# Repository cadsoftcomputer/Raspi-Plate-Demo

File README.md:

# Raspi-Plate-Demo

This is an H-Bridge and IR LED Pi Hat for controlling the Rasperry Pi with an IR Remote Control.

The following sites were instrumental in setting up LIRC and having Python interface with it.
* https://piface.github.io/pifacecad/lirc.html
* http://alexba.in/blog/2013/01/06/setting-up-lirc-on-the-raspberrypi/
* http://ozzmaker.com/2013/10/24/how-to-control-the-gpio-on-a-raspberry-pi-with-an-ir-remote/

This site helped with setting up the Python script to run on boot.
* http://www.raspberrypi-spy.co.uk/2013/07/running-a-python-script-at-boot-using-cron/

The PiHat standard as defined by the Raspberry Pi Foundation
* https://github.com/raspberrypi/hats

All of the Python code was made to run under Python3 however it's likely that it will run under Python2 since the python-lirc library works in both versions of Python.

The EAGLE design files were made using V7 of EAGLE. The PiHat_Standard_Outline.lbr contains packages that conform to the PiHat standard.

For any questions or concerns contact support@cadsoftusa.com or call 954-237-0932.

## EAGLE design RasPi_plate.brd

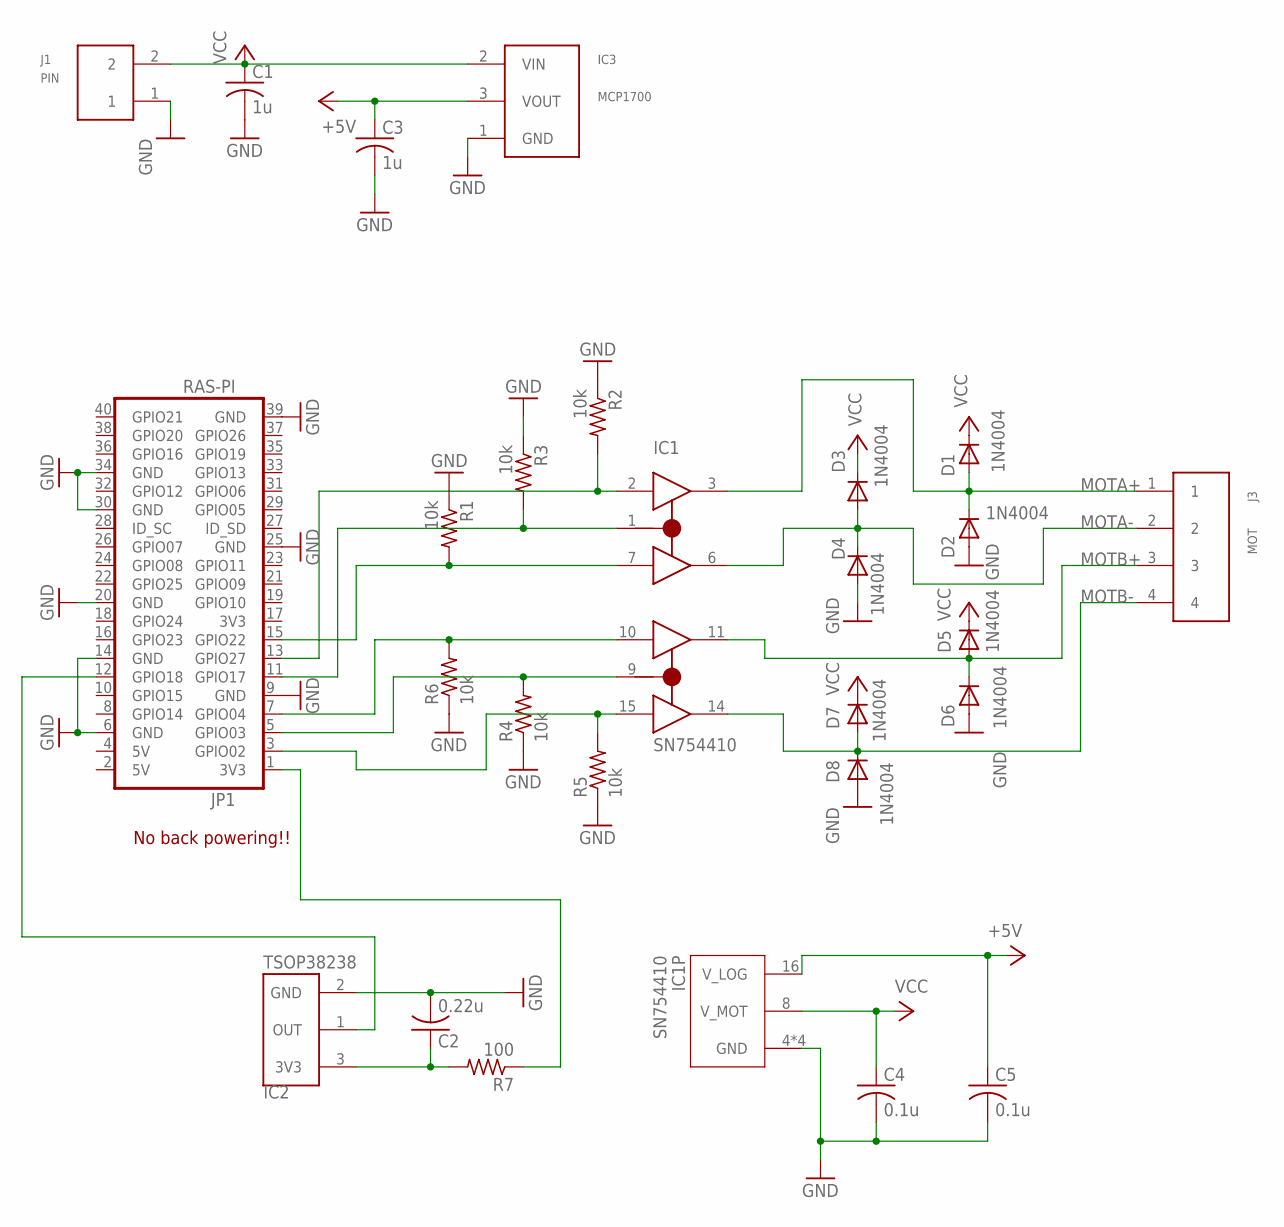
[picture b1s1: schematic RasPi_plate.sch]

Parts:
C1, C3: 1u; C0805; MPN EMK212B7105KD-T
C2: 0.22u; C0805; MPN MC0805B224M250CT
C4, C5: 0.1u; C0805; MPN C2012X7R1H104K085AA
D1, D2, D3, D4, D5, D6, D7, D8: 1N4004; DO41-10; MPN 1N4007-E3/54
IC1: SN754410; DIL16; MPN SN754410NE
IC2: TSOP38238; MPN TSOP38238
IC3: MCP1700; TO92; MPN MCP1700-5002E/TO
J1: PIN; 2PINHEAD
J3: MOT; 4PINHEAD
JP1: RAS-PI; 2X20
R1, R2, R3, R4, R5, R6: 10k; R0805; MPN MCHP05W4F1002T5E
R7: 100; R0805; MPN MCHP05W4F1000T5E

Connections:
1EN: IC1.1 (1,2EN), JP1.11 (GPIO17), R3.2
+3V3: C3.1, C5.1, IC1.16 (V_LOG), IC3.3 (VOUT)
GND: C1.2, C2.2, C3.2, C4.2, C5.2, D2.A, D4.A, D6.A, D8.A, IC1.4 (GND), IC1.5 (GND), IC1.12 (GND), IC1.13 (GND), IC2.2 (GND), IC3.1 (GND), J1.1, JP1.6 (GND), JP1.9 (GND), JP1.14 (GND), JP1.20 (GND), JP1.25 (GND), JP1.30 (GND), JP1.34 (GND), JP1.39 (GND), R1.1, R2.1, R3.1, R4.1, R5.1, R6.1
MOTA+: D1.A, D2.C, IC1.3 (1Y), J3.1
MOTA-: D3.A, D4.C, IC1.6 (2Y), J3.2
MOTB+: D5.A, D6.C, IC1.11 (3Y), J3.3
MOTB-: D7.A, D8.C, IC1.14 (4Y), J3.4
unnamed: IC1.7 (2A), JP1.15 (GPIO22), R1.2
unnamed: IC1.10 (3A), JP1.7 (GPIO04), R6.2
unnamed: IC1.9 (3,4EN), JP1.5 (GPIO03), R4.2
unnamed: IC2.1 (OUT), JP1.12 (GPIO18)
unnamed: C2.1, IC2.3 (3V3), R7.2
unnamed: JP1.1 (3V3), R7.1
unnamed: IC1.2 (1A), JP1.13 (GPIO27), R2.2
unnamed: IC1.15 (4A), JP1.3 (GPIO02), R5.2
VCC: C1.1, C4.1, D1.C, D3.C, D5.C, D7.C, IC1.8 (V_MOT), IC3.2 (VIN), J1.2

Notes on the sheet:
No back powering!!

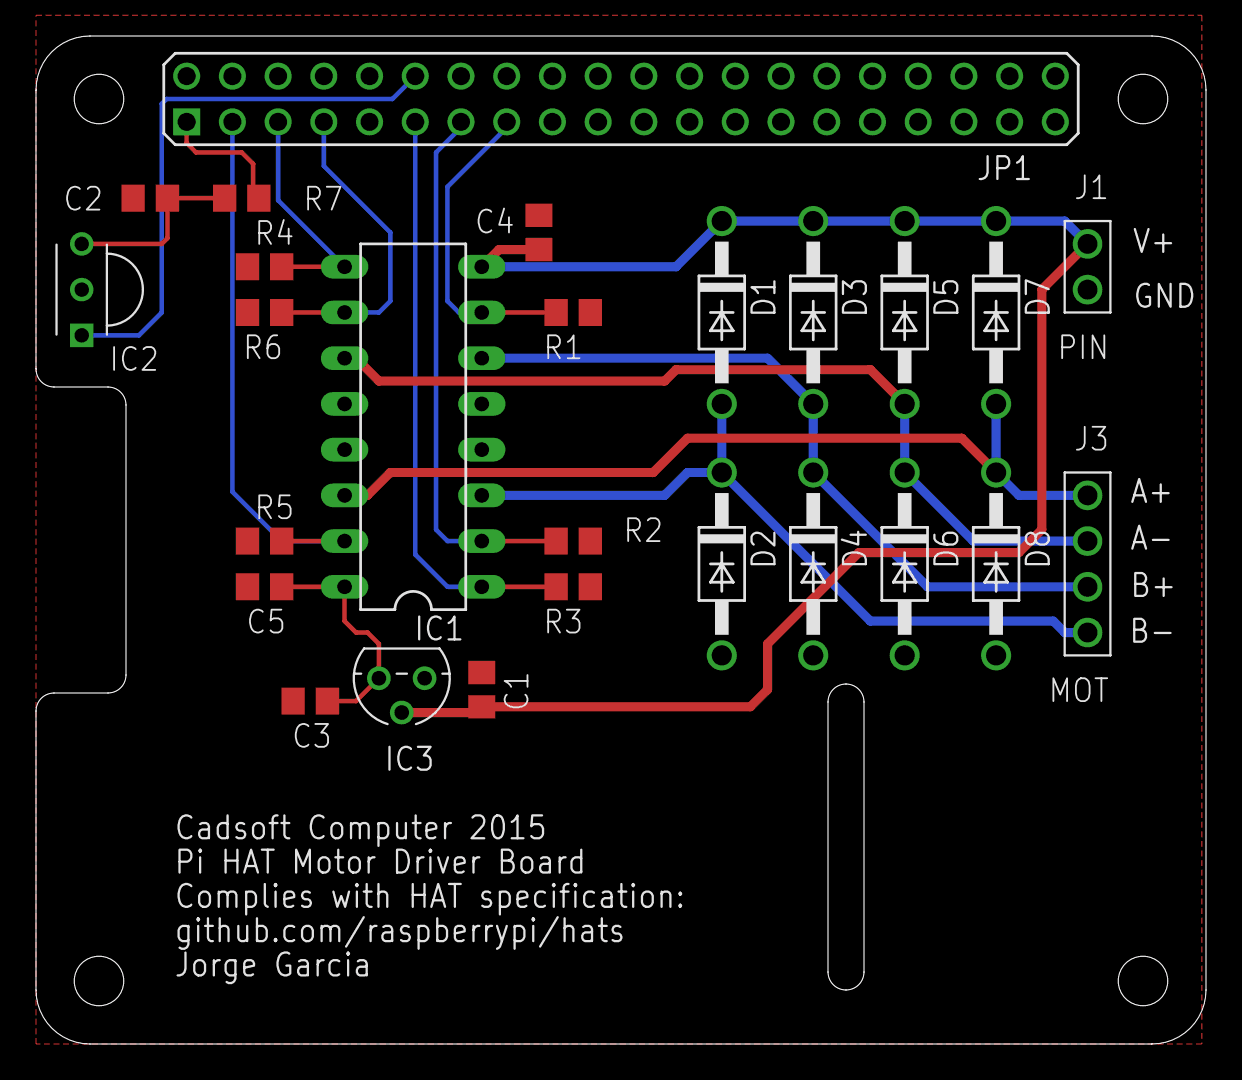
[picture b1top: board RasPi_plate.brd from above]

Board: 2 copper layers, 65.0 x 56.0 mm, 27 parts (0 on the bottom side), 16 nets.

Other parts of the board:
U$1: PI_HAT_STANDARD_TPH

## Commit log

2015-09-09 :boom::camel: Added .gitattributes & .gitignore files
2015-09-17 First commit
    This commit contains the latest release of the project. It includes the
    eagle design files, Python Script, gebers, and the Raspberry Pi config
    files.
2015-09-17 Raspi-Plate-Demo
    Documentation
